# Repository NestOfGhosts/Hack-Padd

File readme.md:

# HackPadd

## A spinoff of a [Hackpad](https://hackpad.hackclub.com/)(A macropad/small keyboard), made by me, for [Hack Club Half Life](https://halflife.hackclub.com/)

## Disclaimer: Havent built this in real life yet. Take this guide as a guide, or wait a couple weeks for me to build it myself

PLACEHOLDER, ADD FINAL PRODUCT IMAGE

I assume you're reading this to make your own. The repos comes in 3 parts: the [chassis](./Chassis%20Cad/) (box you put the pcbs) (3d print/other manufacturing process to make this), the [pcb](./Pcb%20Files/) (Buy from custom pcb seller), and the firmware (the software that translates keystrokes into signals for the computer). It cost around 52~ dollars for me to make.

### Buy the parts

|Part                         |What's For                    |QTY|Unit|Total|Vendor    |
|-----------------------------|------------------------------|---|----|-----|----------|
|Chassis                      |Box                           |1  |6.8 |6.8  |JLC3DP    |
|Pcb                          |pcb bruh                      |5  |1   |5    |PCBWAY    |
|Diodes           1N4148FS-ND |to stop wrong electricity     |12 |0.06|0.72 |Digikey   |
|Seeeduino Xiao Moudle        |Computing                     |1  |5.67|5.67 |Digikey   |
|Switches                     |switching                     |20 |0.26|5.2  |Aliexpress|
|Keycaps                      |capping those keys            |30 |0.41|12.3 |Aliexpress|
|Subtotal                     |For accountants               |   |    |35.69|          |
|Shipping and stuff           |Cuz i dont live in a warehouse|   |    |16.65|          |
|                             |                              |   |    |52.34|          |

(these are my personal prices, in usd, shipped to canada)

- Seeduino Moudle Xiao: the microcontroller that holds the firmware (I'm getting mine from [digikey](https://www.digikey.ca/en/products/detail/seeed-technology-co-ltd/102010328/11506471)). Make sure that the one you get has pins so that you can solder it onto the board

- 12 1N4148 diodes (im getting from [digikey](https://www.digikey.ca/en/products/detail/onsemi/1N4148/458603)).

- Chassis: 3d print it ideally. You can use other ways to make a box with a plate to hold the keys, but you may need to edit the 3d models to accomadate for your method. If you dont have a 3d printer you should look around your local area for a print farm. I'm getting mine printed in JLC3DP. You can print it with the .step file in [Chassis Cad](./Chassis%20Cad/chassis.step)

- Pcb: Find a pcb printing company and buy one from them based on the gerber files in [Pcb Files](./Pcb%20Files/). I'm getting mine from PCBWay. Ideally use 1.6mm thick pcbs

- 12 Keyswitches + Keycaps: I just got mine from amazon, make sure they work with cherry mx 3 pins

- You're also going to need to know how to solder, and own a soldering iron

### Assembly

1. Flash the [firmware](./Firmware/hackpadd.uf2): 
    - Download the file (extract if needed)
    - Connect the moudle xiao to your computer
    - Short the two rst pins on the seeeduino twice in succession to put it into bootloader mode

    (for more info on this step go to [seeduino's wiki](https://wiki.seeedstudio.com/Seeeduino-XIAO/) and scroll down until you see "Enter Bootloader Mode" and "For Xiao SAMD21")
    - A new drive should appear in your file manager. Simply move the .uf2 file into the Seeduino and wait for the file to disappear. When you can no longer see the uf2 the firmware is loaded
2. Solder the Xiao onto the pcb
    - If you don't know how to solder, I recommend youtube as a starting point.
    - You *should* only be doing through hole soldering. 
    - Make sure the seeduino is in the right place and orientation.
    - The seeduino should be on the backside of the pcb, near the top to the right (on the back)

    (Frontside)

    (Backside)

4. Solder the keys and diodes
    - Diodes on the backside, switches on the front
5. Assemble (actually this time)
    - pcb in chassis, plate on top, insert the tubes in the holes

    wow your did it

### How it works

The macropad has 3 "layers". Basically, the macropad (with 12 keys) has 12 different actions for each key  
[Alt + Tab] [Show desktop] [Task Manager]  
[Previous song/video/media] [Pause] [Next]  
[Copy] [Cut] [Paste]  
[Undo] [Redo] [Hold to access next layer]  

See that "hold to access" key? While holding that key you get access to a new suite of actions  
[f13] [f14] [f15]  
[f16] [f17] [f18]  
[f19] [f20] [f21]  
[Hold to access next layer] [nothing] [nothing, you should already have this key down to access this layer]

Notice another hta key? There's a third layer  
[Bootloader (so you can enter bootloader without needing to short the rst bits)] [nothing] [nothing]  
[Nothing in entire 2nd line]  
[Power off] [nothing] [nothing]  
[You should already be holding this key down] [nothing] [You should already be holding this down].

3 layers :3

### Customization
If you want to make your own key's, you need to make your own firmware. The easiest way to do this is to clone [my firmware repo](https://github.com/NestOfGhosts/Hack-Padd-Firmware), and edit the file config/hackpadd.keymap  
  
(This is what the top of the file should look like)

(Notice how inside of bindings = <> there are 3 columns and 4 rows of characters? They match up to the 3 columns and 4 rows of the macropad.)
The &kp and &mo etc's definition's can be found in [ZMK.dev Docs](https://zmk.dev/docs/keymaps/behaviors), where you can also find other actions you can bind to the keys.

(Notice the 0{
    bindings = <>
}? This is layer one (The 0 is just a name/label i put on the layer. The actual order of layer's is based on it's position in the file))
In the actual .keymap folder you'll see a layer 0{}, 1{}, and 2{}. Feel free to add, delete, or rename the layers. For more info on keymap customization, read [the zmk.dev doc keymap section](https://zmk.dev/docs/keymaps) 

When you're done editing the .keymap, upload your modifications to github. Then, go to the "actions" tab 
  
In the actions tab, you should see the commit(a version of your github repo) you uploaded onto github under "All workflows". Wait for it to finish processing. When it's done processing you should see either a red x or a green checkmark. If it's a green checkmark, click on the commit name, then scroll down to "artifacts", where you should find a firmware file. 

Simply download and extract the file, and you get your very own customized .uf2

If it was a red x, it means that the firmware builder failed. If you're a beginner I recommend asking someone/ai for help, but the main error you would encounter is under "West Build (hackpadd-seeeduino_xiao//zmk)". Simply scroll through the error message until you find a message that says: 
 (Prolly with different numbers) or something similar.  
In my case, it means that there's a typo that starts in line 10, 53 characters to the right. To fix the typo, just match the different elements in that line of code to the example code in the [ZMK.dev Docs](https://zmk.dev/docs/keymaps/behaviors).

If it's something else, ask someone/ai. If you're in hack club, you can try asking someone in the hack club slack.

If instead you wanted to customize the hardware (more/less keys, change layout, change drawings), I recommend just following the guide at [Hackpad.Hackclub](https://hackpad.hackclub.com/) to make your own, cause the existing hardware is an invention of a me from the past, and I cannot decipher his work.

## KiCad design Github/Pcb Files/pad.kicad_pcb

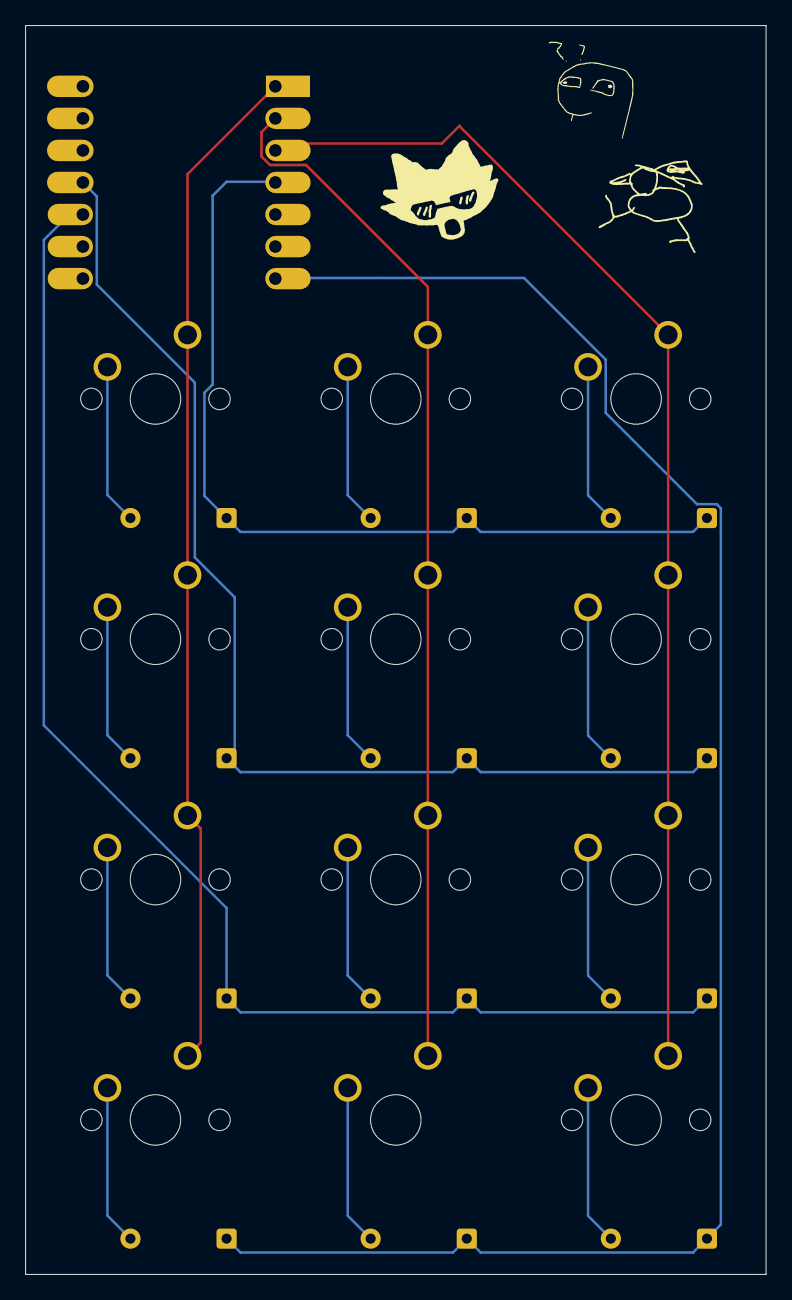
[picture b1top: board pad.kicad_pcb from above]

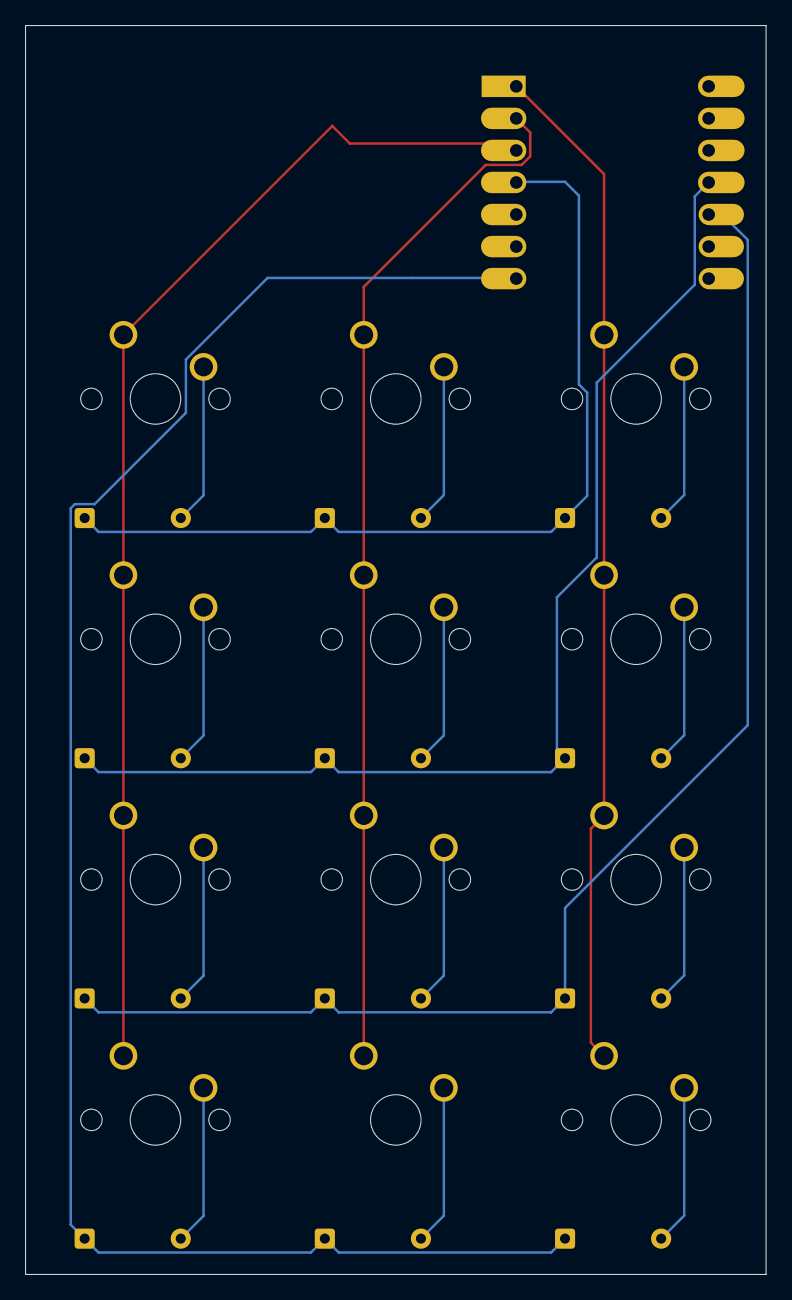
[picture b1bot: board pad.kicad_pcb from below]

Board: 2 copper layers, 58.7 x 99.0 mm, 25 parts (13 on the bottom side), 19 nets.

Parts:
D1, D3, D4, D5, D6, D7, D8, D9, D10, D11, D12, D13: D; D_DO-35_SOD27_P7.62mm_Horizontal
SW1, SW2, SW3, SW4, SW5, SW6, SW7, SW9, SW10, SW11, SW12: SW_Push; SW_Cherry_MX_1.00u_PCB
SW8: SW_Push; SW_Cherry_MX_1.00u_Plate
U1: MOUDLE-SEEEDUINO-XIAO; XIAO-Generic-Hybrid-14P-2.54-21X17.8MM

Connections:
/Column1: SW1.1, SW2.1, SW3.1, SW4.1, U1.1 (PA02_A0_D0)
/Column2: SW5.1, SW6.1, SW7.1, SW8.1, U1.2 (PA4_A1_D1)
/Column3: SW9.1, SW10.1, SW11.1, SW12.1, U1.3 (PA10_A2_D2)
/Row1: D1.1 (K), D6.1 (K), D10.1 (K), U1.4 (PA11_A3_D3)
/Row2: D3.1 (K), D7.1 (K), D11.1 (K), U1.11 (PA6_A10_D10_MOSI)
/Row3: D4.1 (K), D8.1 (K), D12.1 (K), U1.10 (PA5_A9_D9_MISO)
/Row4: D5.1 (K), D9.1 (K), D13.1 (K), U1.7 (PB08_A6_D6_TX)
unnamed: D1.2 (A), SW1.2
unnamed: D3.2 (A), SW2.2
unnamed: D4.2 (A), SW3.2
unnamed: D5.2 (A), SW4.2
unnamed: D6.2 (A), SW5.2
unnamed: D7.2 (A), SW6.2
unnamed: D8.2 (A), SW7.2
unnamed: D9.2 (A), SW8.2
unnamed: D10.2 (A), SW9.2
unnamed: D11.2 (A), SW10.2
unnamed: D12.2 (A), SW11.2
unnamed: D13.2 (A), SW12.2
